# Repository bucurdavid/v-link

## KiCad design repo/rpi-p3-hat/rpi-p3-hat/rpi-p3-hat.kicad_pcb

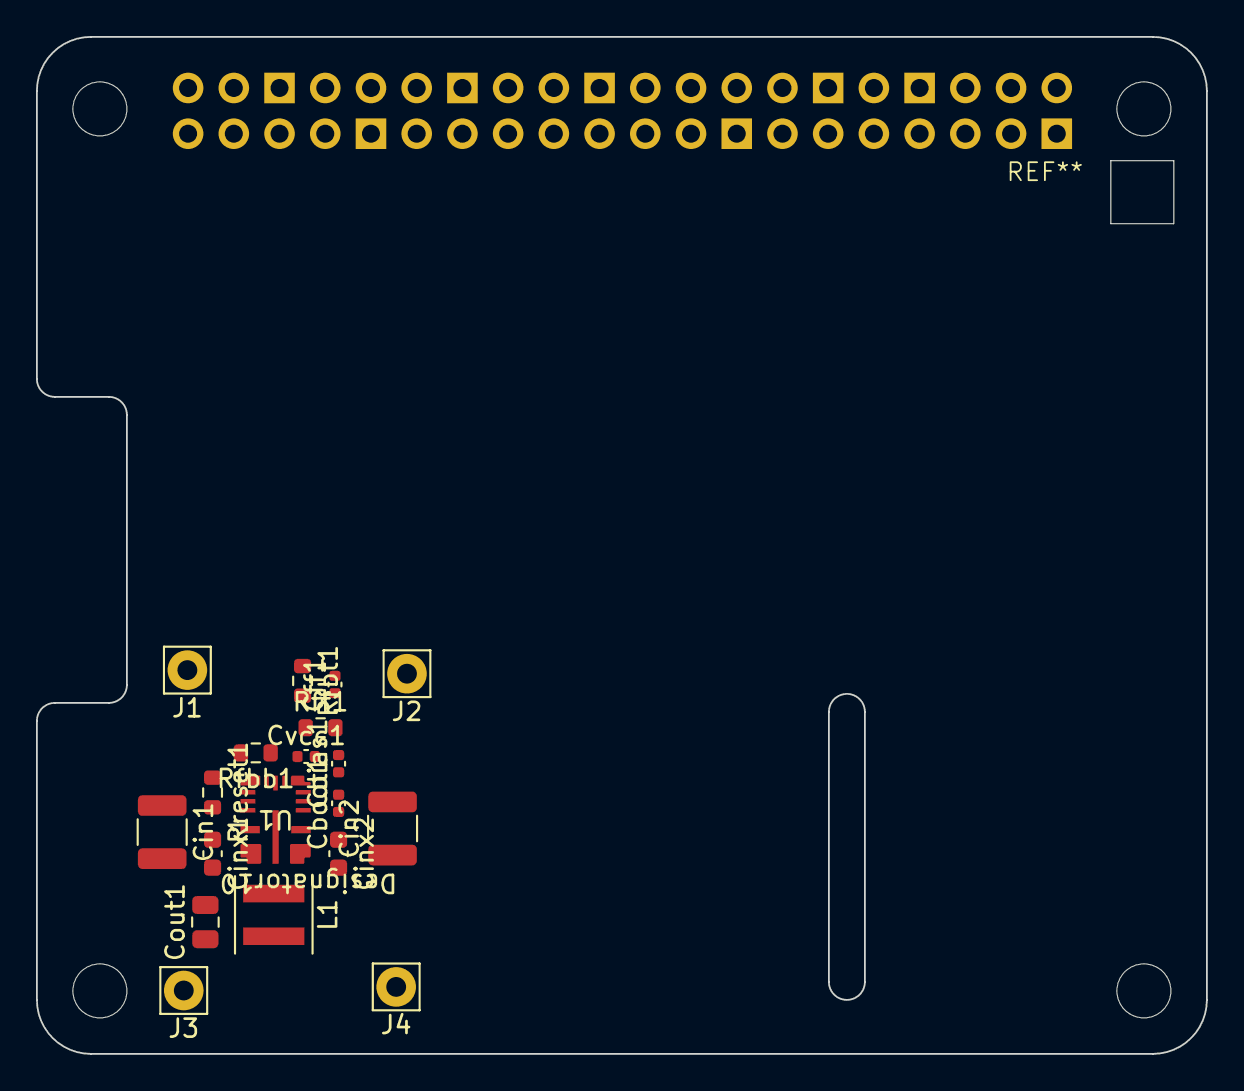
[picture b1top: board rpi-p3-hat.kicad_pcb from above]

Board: 4 copper layers, 65.0 x 56.5 mm, 19 parts (0 on the bottom side), 9 nets, no tracks yet.

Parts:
Cbias1: 100nF; C_0402_1005Metric
Cboot1: 100nF; C_0402_1005Metric
Cff1: 7.5pF; C_0402_1005Metric
Cin1, Cin2: 10uF; C_1210_3225Metric
Cinx1, Cinx2: 1uF; C_0603_1608Metric
Cout1: 47uF; C_0805_2012Metric
Cvcc1: 1uF; C_0402_1005Metric
J1, J2, J3, J4: Conn_01x01_Pin; Pin_D1.1mm_L8.5mm_W2.5mm_FlatFork
L1: 1uH; L_Coilcraft_XxL4020
Rfbb1: 24.9k; R_0603_1608Metric
Rfbt1: 100k; R_0603_1608Metric
Rff1: 4.99k; R_0603_1608Metric
Rreset1: 100k; R_0603_1608Metric
U1: LM62460RPHR; RPH0016A

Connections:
/SW: Cboot1.1, L1.1, U1.16 (SW)
/VIN: Cin1.1, Cin2.1, Cinx1.1, Cinx2.1, J1.1, U1.2 (VIN), U1.13 (EN), U1.14 (VIN)
/VOUT: Cbias1.1, Cff1.1, Cout1.1, J3.1, L1.2, Rfbt1.1, Rreset1.2, U1.5 (BIAS)
GND: Cbias1.2, Cin1.2, Cin2.2, Cinx1.2, Cinx2.2, Cout1.2, Cvcc1.2, J2.1, J4.1, Rfbb1.2, U1.1 (PGND), U1.8 (AGND), U1.9 (RT), U1.11 (SpSp), U1.12 (SYNC_MODE), U1.15 (PGND)
unnamed: Cff1.2, Rff1.2
unnamed: Cboot1.2, U1.3 (RBOOT), U1.4 (CBOOT)
unnamed: Rfbb1.1, Rfbt1.2, Rff1.1, U1.7 (FB)
unnamed: Rreset1.1, U1.10 (RESET)
unnamed: Cvcc1.1, U1.6 (VCC)

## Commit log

2024-05-19 Automatically connect default namespace, add some python requirements
2024-10-09 fix: use local repo
2024-10-09 feat: change splash screen
2024-10-09 fix: comment lin
2024-11-11 feat: schematics for rpi p3 hat
2024-11-12 feat: latest hat changes
